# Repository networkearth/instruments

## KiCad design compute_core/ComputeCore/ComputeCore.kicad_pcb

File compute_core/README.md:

# Compute Core

## Requirements

Connections: 
- UART for communication with non-programming devices (2)
- SWD for communication with programming devices (2)
- RST for resetting (1)
- Clock Power (can always be present) (1)
- Power (1)
- GND
(8 pins total)

- Multiplexed I2C (16-2)
  - Programmable address
(14 pins total) 

- Connections for Radio Link (?)
We'll leave this one out for now as this will be a whole adventure unto itself. 

Peripherals
- Real time clock
- External Flash Memory
- Multiplexer for I2C
- LEDs for status

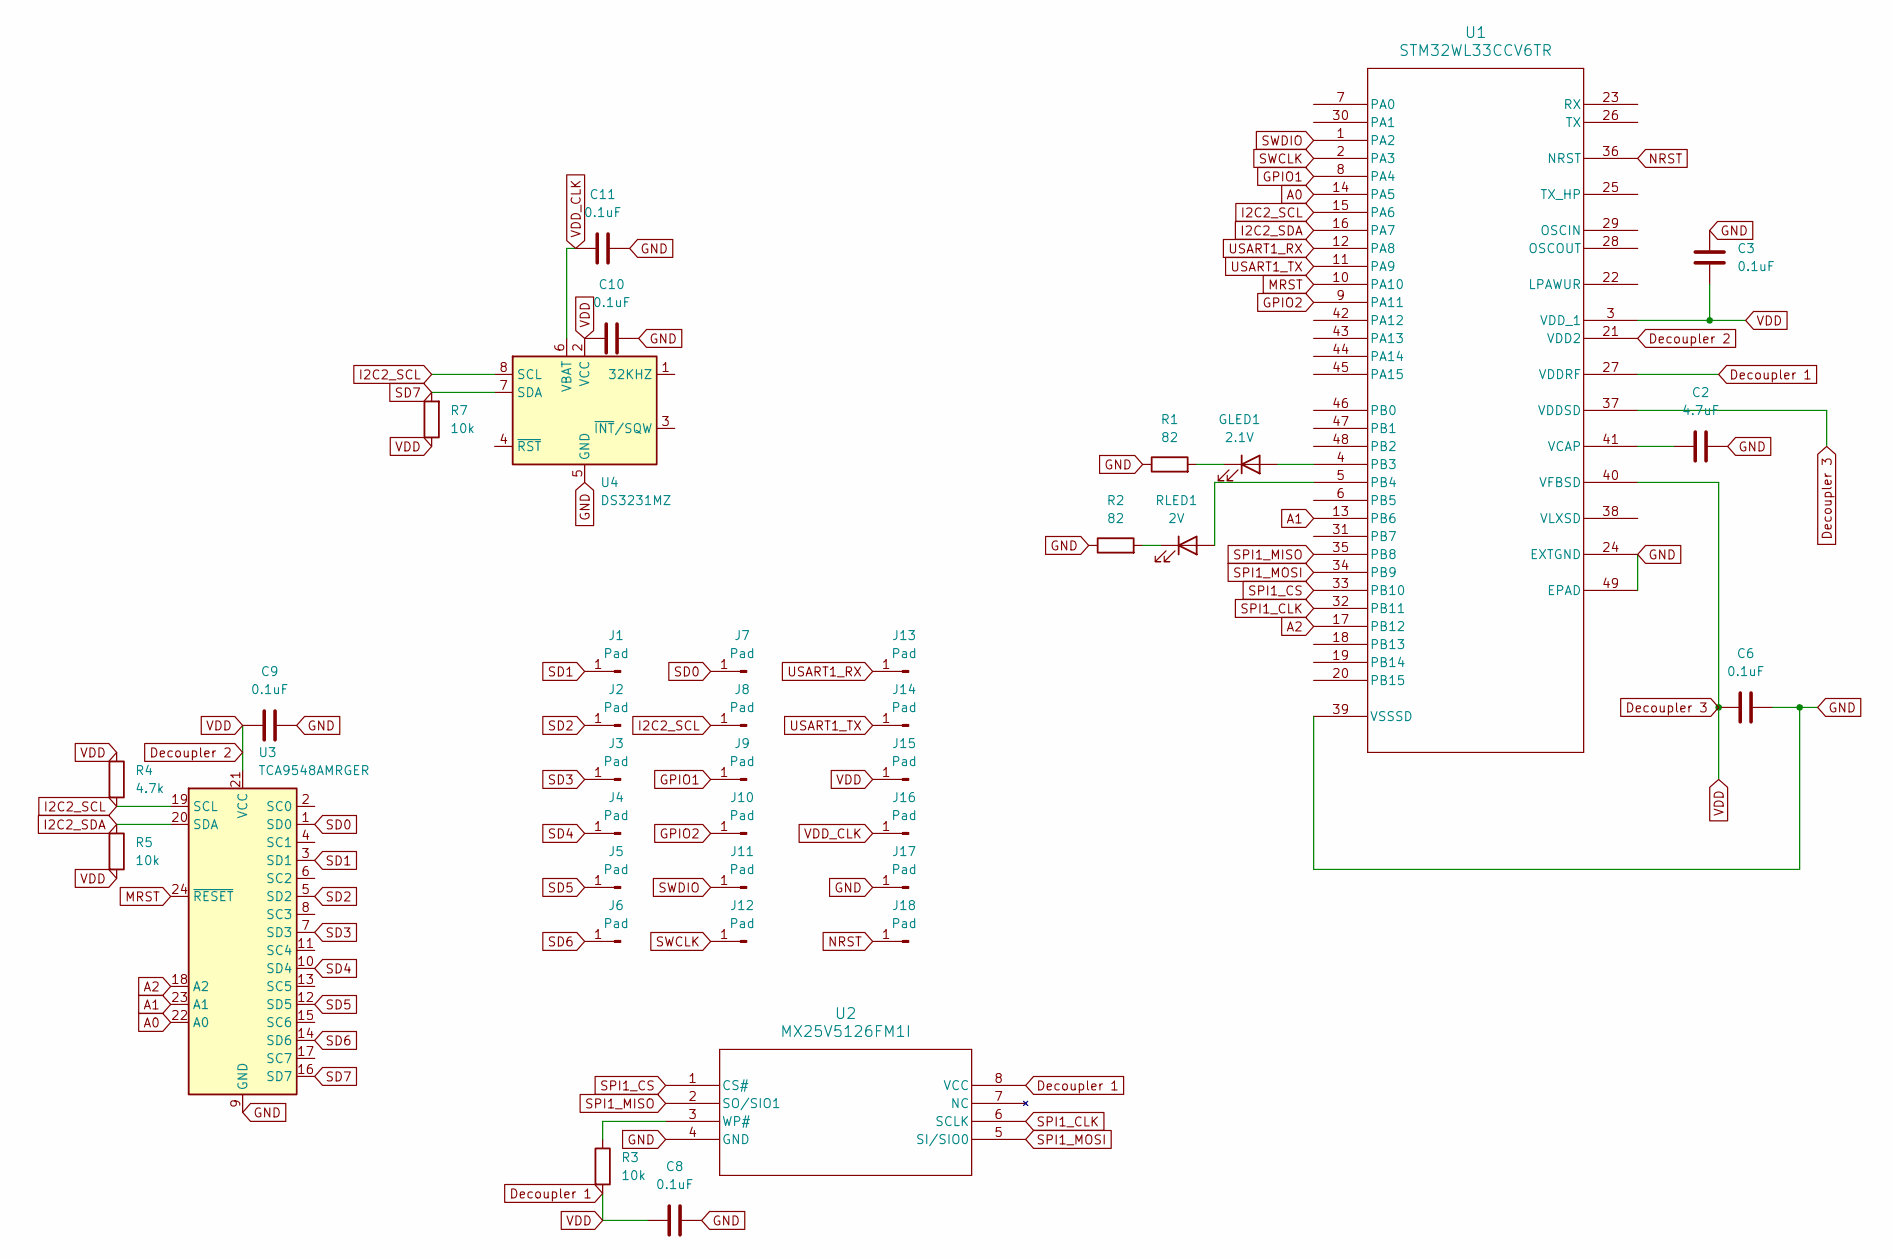
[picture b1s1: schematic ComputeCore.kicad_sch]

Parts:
C2: 4.7uF; C_0201_0603Metric
C3, C6, C8, C9, C10, C11: 0.1uF; C_0201_0603Metric
GLED1: 2.1V; LED_0201_0603Metric
J1, J2, J3, J4, J5, J6, J7, J8, J9, J10, J11, J12, J13, J14, J15, J16, J17, J18: Pad; SolderWire-0.1sqmm_1x01_D0.4mm_OD1mm
R1, R2: 82; R_0201_0603Metric
R3, R5, R7: 10k; R_0201_0603Metric
R4: 4.7k; R_0201_0603Metric
RLED1: 2V; LED_0201_0603Metric
U1: STM32WL33CCV6TR; VFQFPN-48_6x6x0p9mm_STM
U2: MX25V5126FM1I; 8-SOP_MX25V_M1_MAC
U3: TCA9548AMRGER; Texas_RGE0024C_VQFN-24-1EP_4x4mm_P0.5mm_EP2.1x2.1mm
U4: DS3231MZ; SOIC-8_3.9x4.9mm_P1.27mm

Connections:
A0: U1.14 (PA5), U3.22 (A0)
A1: U1.13 (PB6), U3.23 (A1)
A2: U1.17 (PB12), U3.18 (A2)
Decoupler 1: C3.2, C6.1, C8.1, C9.1, C10.1, J15.1, R3.2, R4.1, R5.2, R7.1, U1.3 (VDD_1), U1.21 (VDD2), U1.27 (VDDRF), U1.37 (VDDSD), U1.40 (VFBSD), U2.8 (VCC), U3.21 (VCC), U4.2 (VCC)
GND: C2.2, C3.1, C6.2, C8.2, C9.2, C10.2, C11.2, J17.1, R1.1, R2.1, U1.24 (EXTGND), U1.39 (VSSSD), U1.49 (EPAD), U2.4 (GND), U3.9 (GND), U4.5 (GND)
GPIO1: J9.1, U1.8 (PA4)
GPIO2: J10.1, U1.9 (PA11)
I2C2_SCL: J8.1, R4.2, U1.15 (PA6), U3.19 (SCL), U4.8 (SCL)
I2C2_SDA: R5.1, U1.16 (PA7), U3.20 (SDA)
MRST: U1.10 (PA10), U3.24 (~RESET)
NRST: J18.1, U1.36 (NRST)
unnamed: GLED1.2 (A), U1.4 (PB3)
unnamed: GLED1.1 (K), R1.2
unnamed: RLED1.2 (A), U1.5 (PB4)
unnamed: R2.2, RLED1.1 (K)
unnamed: C2.1, U1.41 (VCAP)
unnamed: R3.1, U2.3 (WP#)
SD0: J7.1, U3.1 (SD0)
SD1: J1.1, U3.3 (SD1)
SD2: J2.1, U3.5 (SD2)
SD3: J3.1, U3.7 (SD3)
SD4: J4.1, U3.10 (SD4)
SD5: J5.1, U3.12 (SD5)
SD6: J6.1, U3.14 (SD6)
SD7: R7.2, U3.16 (SD7), U4.7 (SDA)
SPI1_CLK: U1.32 (PB11), U2.6 (SCLK)
SPI1_CS: U1.33 (PB10), U2.1 (CS#)
SPI1_MISO: U1.35 (PB8), U2.2 (SO/SIO1)
SPI1_MOSI: U1.34 (PB9), U2.5 (SI/SIO0)
SWCLK: J12.1, U1.2 (PA3)
SWDIO: J11.1, U1.1 (PA2)
USART1_RX: J13.1, U1.12 (PA8)
USART1_TX: J14.1, U1.11 (PA9)
VDD_CLK: C11.1, J16.1, U4.6 (VBAT)

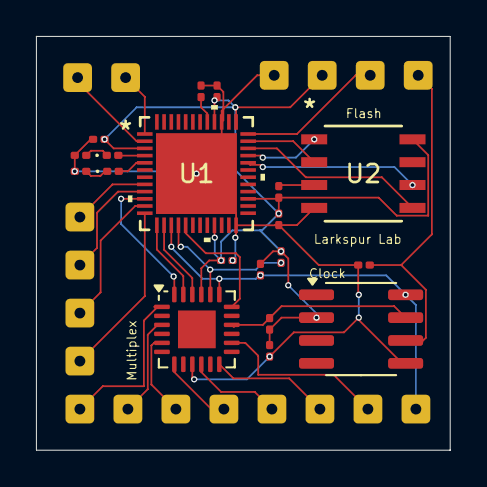
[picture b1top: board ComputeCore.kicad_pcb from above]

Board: 2 copper layers, 23.0 x 23.0 mm, 37 parts (0 on the bottom side), 34 nets.

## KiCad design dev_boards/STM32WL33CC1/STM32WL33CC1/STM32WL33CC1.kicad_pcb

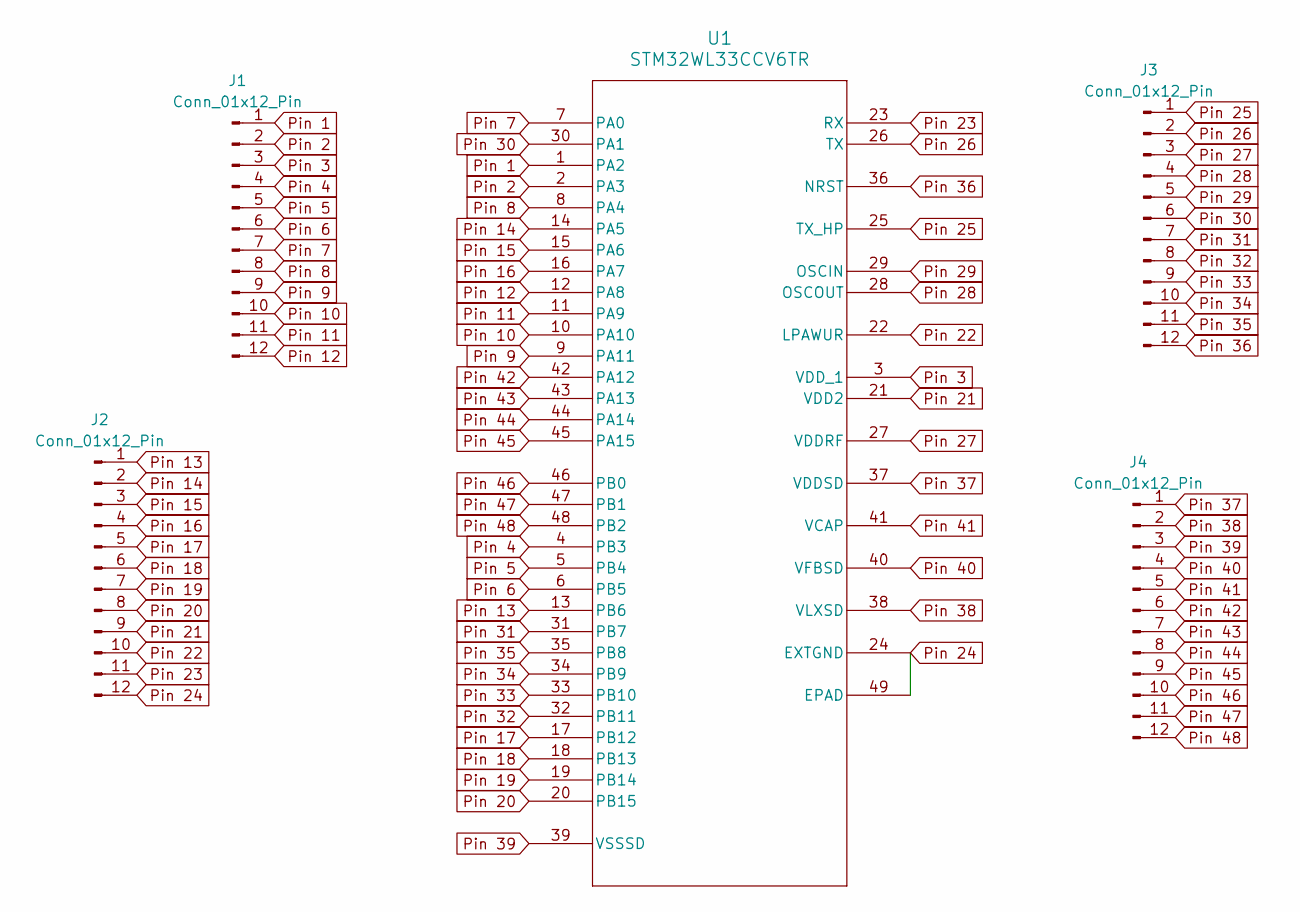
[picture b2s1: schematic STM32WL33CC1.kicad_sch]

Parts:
J1, J2, J3, J4: Conn_01x12_Pin; PinHeader_1x12_P2.54mm_Vertical
U1: STM32WL33CCV6TR; VFQFPN-48_6x6x0p9mm_STM

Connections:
Pin 1: J1.1, U1.1 (PA2)
Pin 2: J1.2, U1.2 (PA3)
Pin 3: J1.3, U1.3 (VDD_1)
Pin 4: J1.4, U1.4 (PB3)
Pin 5: J1.5, U1.5 (PB4)
Pin 6: J1.6, U1.6 (PB5)
Pin 7: J1.7, U1.7 (PA0)
Pin 8: J1.8, U1.8 (PA4)
Pin 9: J1.9, U1.9 (PA11)
Pin 10: J1.10, U1.10 (PA10)
Pin 11: J1.11, U1.11 (PA9)
Pin 12: J1.12, U1.12 (PA8)
Pin 13: J2.1, U1.13 (PB6)
Pin 14: J2.2, U1.14 (PA5)
Pin 15: J2.3, U1.15 (PA6)
Pin 16: J2.4, U1.16 (PA7)
Pin 17: J2.5, U1.17 (PB12)
Pin 18: J2.6, U1.18 (PB13)
Pin 19: J2.7, U1.19 (PB14)
Pin 20: J2.8, U1.20 (PB15)
Pin 21: J2.9, U1.21 (VDD2)
Pin 22: J2.10, U1.22 (LPAWUR)
Pin 23: J2.11, U1.23 (RX)
Pin 24: J2.12, U1.24 (EXTGND), U1.49 (EPAD)
Pin 25: J3.1, U1.25 (TX_HP)
Pin 26: J3.2, U1.26 (TX)
Pin 27: J3.3, U1.27 (VDDRF)
Pin 28: J3.4, U1.28 (OSCOUT)
Pin 29: J3.5, U1.29 (OSCIN)
Pin 30: J3.6, U1.30 (PA1)
Pin 31: J3.7, U1.31 (PB7)
Pin 32: J3.8, U1.32 (PB11)
Pin 33: J3.9, U1.33 (PB10)
Pin 34: J3.10, U1.34 (PB9)
Pin 35: J3.11, U1.35 (PB8)
Pin 36: J3.12, U1.36 (NRST)
Pin 37: J4.1, U1.37 (VDDSD)
Pin 38: J4.2, U1.38 (VLXSD)
Pin 39: J4.3, U1.39 (VSSSD)
Pin 40: J4.4, U1.40 (VFBSD)
Pin 41: J4.5, U1.41 (VCAP)
Pin 42: J4.6, U1.42 (PA12)
Pin 43: J4.7, U1.43 (PA13)
Pin 44: J4.8, U1.44 (PA14)
Pin 45: J4.9, U1.45 (PA15)
Pin 46: J4.10, U1.46 (PB0)
Pin 47: J4.11, U1.47 (PB1)
Pin 48: J4.12, U1.48 (PB2)

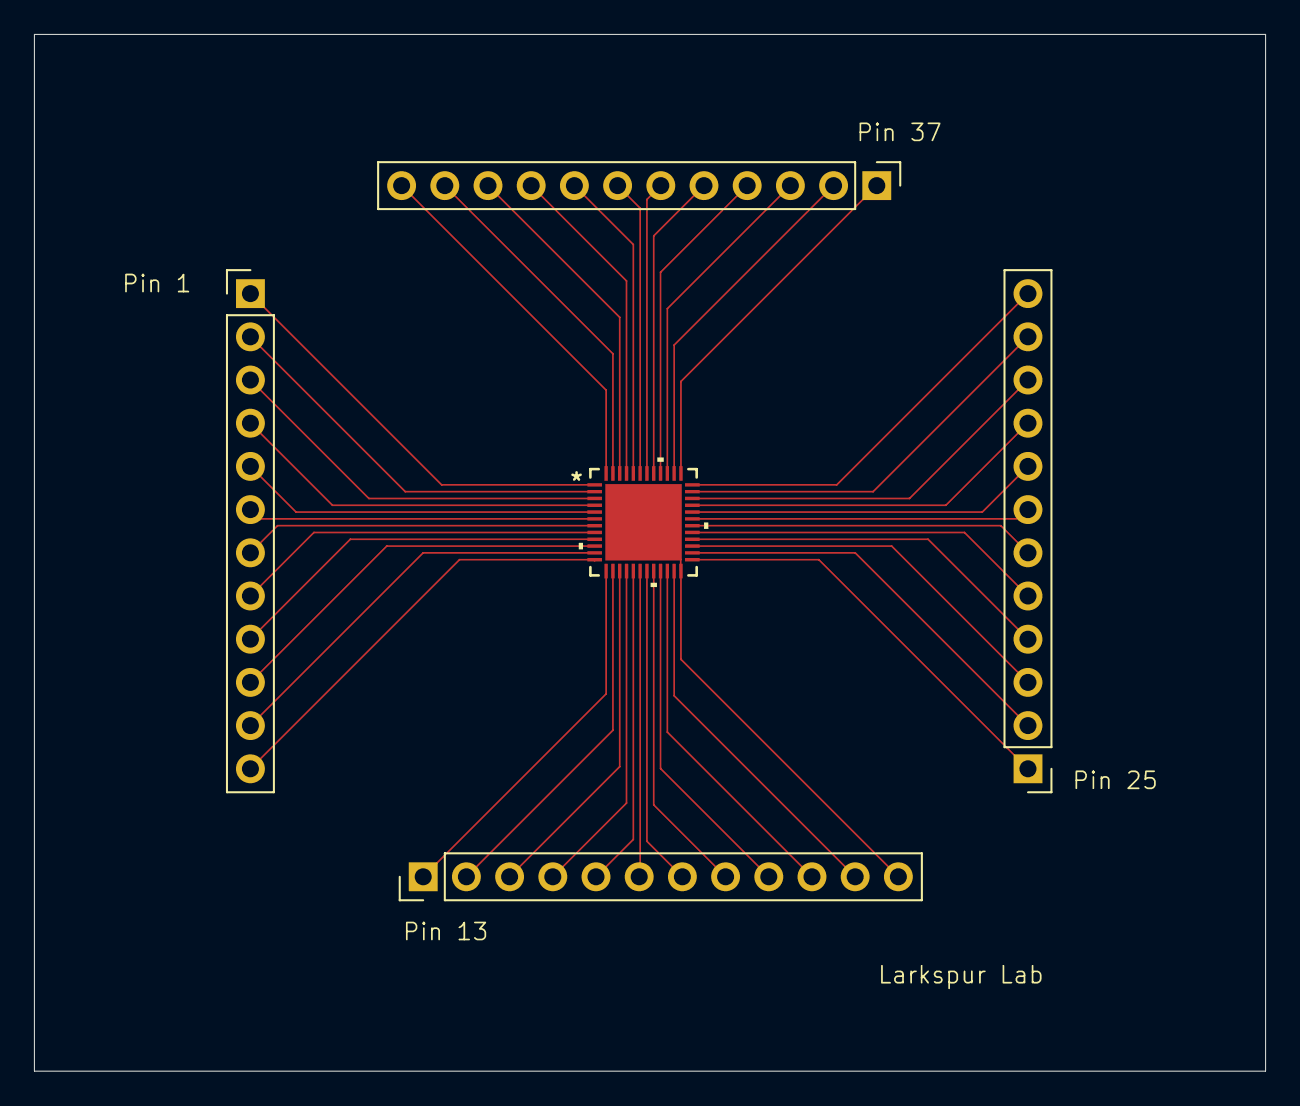
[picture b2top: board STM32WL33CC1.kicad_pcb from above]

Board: 2 copper layers, 72.4 x 61.0 mm, 5 parts (0 on the bottom side), 48 nets.

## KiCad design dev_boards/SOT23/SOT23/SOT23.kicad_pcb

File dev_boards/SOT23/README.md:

# Bits and Bobs

Loads of things come in an **SOT23** package.

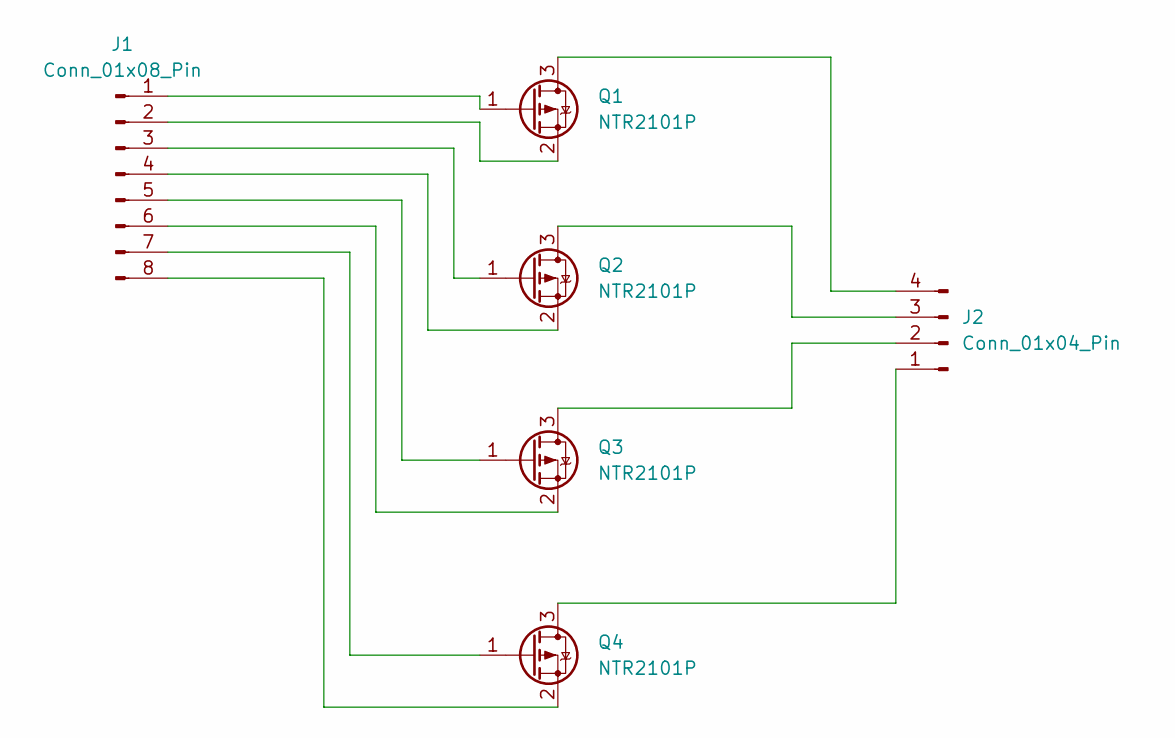
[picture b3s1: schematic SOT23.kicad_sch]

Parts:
J1: Conn_01x08_Pin; PinHeader_1x08_P2.54mm_Vertical
J2: Conn_01x04_Pin; PinHeader_1x04_P2.54mm_Vertical
Q1, Q2, Q3, Q4: NTR2101P; SOT-23

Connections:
unnamed: J1.1, Q1.1 (G)
unnamed: J1.2, Q1.2 (S)
unnamed: J1.3, Q2.1 (G)
unnamed: J1.4, Q2.2 (S)
unnamed: J1.5, Q3.1 (G)
unnamed: J1.6, Q3.2 (S)
unnamed: J1.7, Q4.1 (G)
unnamed: J1.8, Q4.2 (S)
unnamed: J2.1, Q4.3 (D)
unnamed: J2.2, Q3.3 (D)
unnamed: J2.3, Q2.3 (D)
unnamed: J2.4, Q1.3 (D)

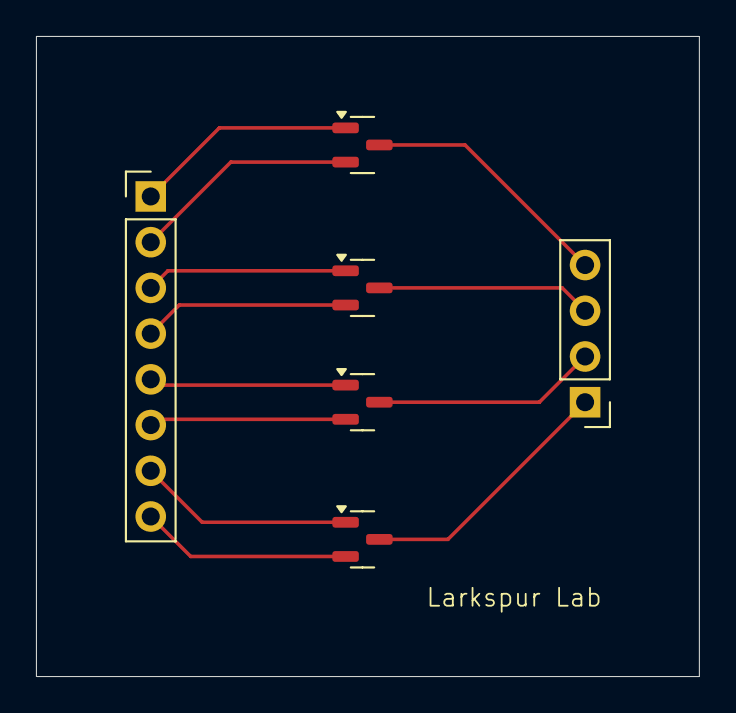
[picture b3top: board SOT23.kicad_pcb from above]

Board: 2 copper layers, 36.8 x 35.6 mm, 6 parts (0 on the bottom side), 12 nets.

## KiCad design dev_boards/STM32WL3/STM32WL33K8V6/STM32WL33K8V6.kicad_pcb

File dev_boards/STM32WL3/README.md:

# Microcontroller Unit (MCU)

Digital radio communication is fantastically interesting and like many fascinating things it is pretty darn complicated. So isn't it wonderful that ST has chips and software that come with everything you need to manage the communication! All at low power too.

- [STM32WL3 Line](https://www.st.com/content/st_com/en/campaigns/stm32wl3-comprehensive-ecosystem-long-range-iot-connectivity-z13.html?ecmp=tt45044_gl_ps_jun2025&aw_kw=stm32%20wireless%20mcus&aw_m=e&aw_c=22032657977&aw_tg=aud-2173644794635:kwd-1457438729886&aw_gclid=CjwKCAjwprjDBhBTEiwA1m1d0oSMdFI7UCsje4d8FfuBJjFW-EInW3rT8UjZ1rWWHqVwe16UJWC6EBoCuuIQAvD_BwE&gad_source=1&gad_campaignid=22032657977&gbraid=0AAAAADmP1XT8bcmLf6zb8UZTWm7Z2yrFH&gclid=CjwKCAjwprjDBhBTEiwA1m1d0oSMdFI7UCsje4d8FfuBJjFW-EInW3rT8UjZ1rWWHqVwe16UJWC6EBoCuuIQAvD_BwE)
- [Kineis Constellation](https://blog.st.com/kineis/) (works with STM32's)
- [Kineis Stack](https://www.st.com/content/st_com/en/partner/partner-program/partnerpage/Kineis.html)
- [Reference Design](https://kineis.com/en/kineis-stack-for-a-quick-integration-2/)
- [and it's part of the CLS (Argos) ecosystem!](https://telemetry.groupcls.com/argos-solutions/argos-products/modems/)

All in all pretty sweet. What we need is one that's integrated with I2C and SPI for communication with sensors and memory as well. The [STM32WL33K8V6](https://www.digikey.com/en/products/detail/stmicroelectronics/STM32WL33K8V6/22519707) fits the bill pretty well. This uses a **32-VFQFN Exposed Pad** footprint so we can reuse this development board for anything with this footprint.

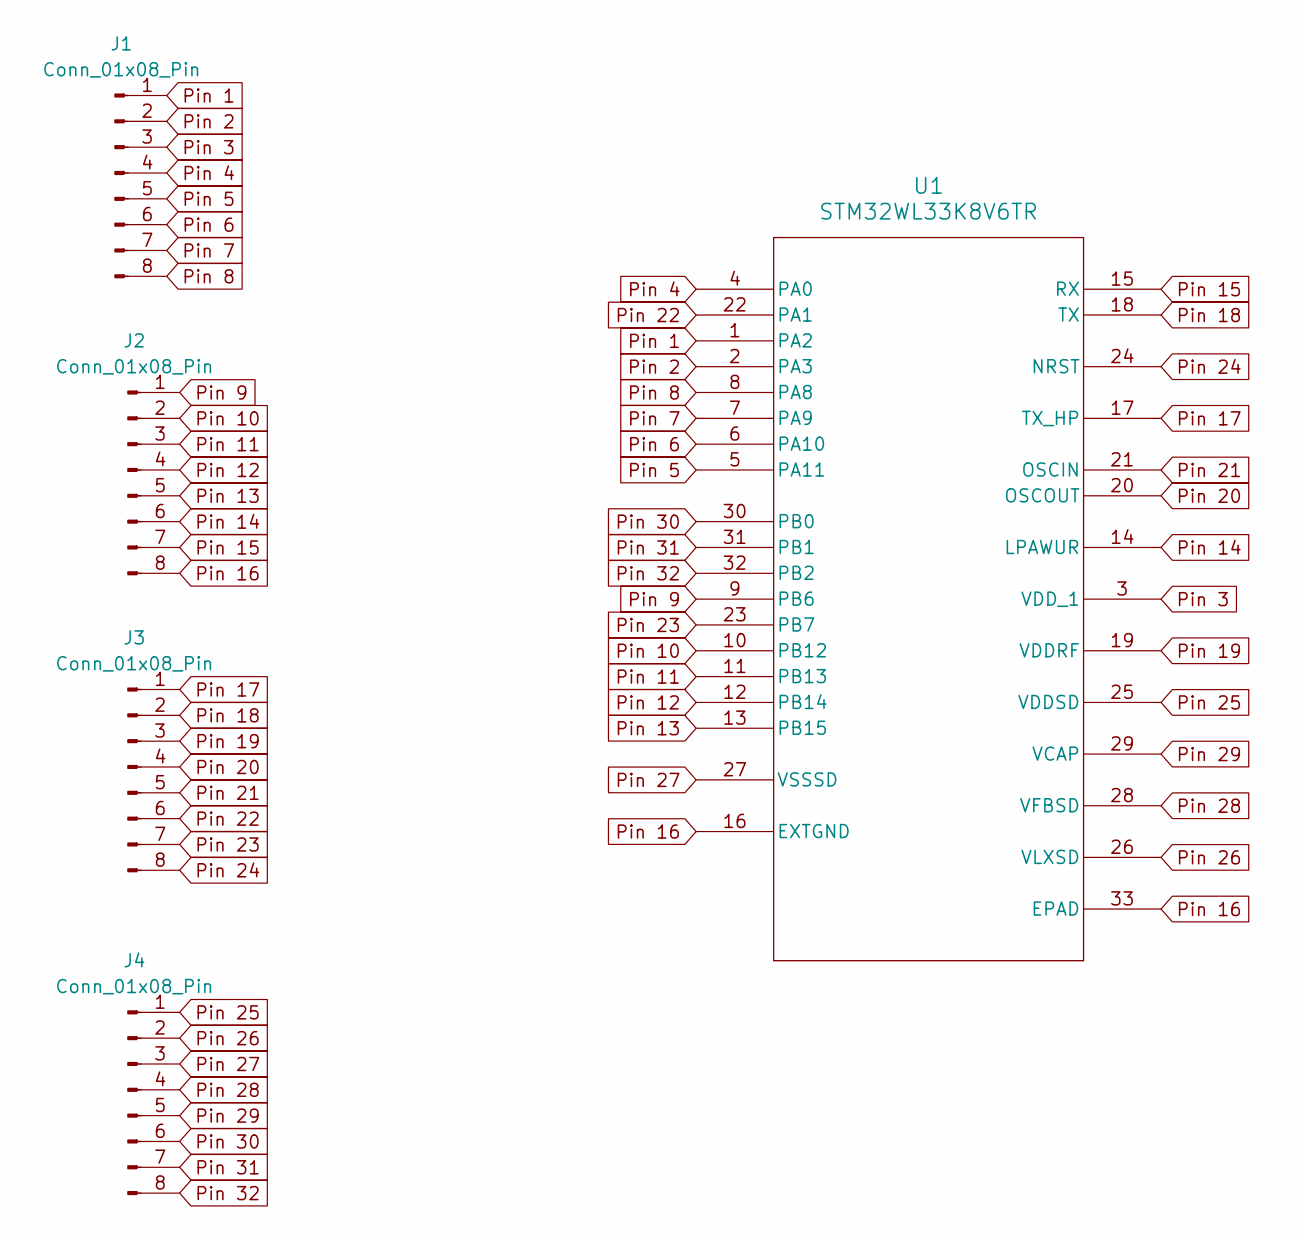
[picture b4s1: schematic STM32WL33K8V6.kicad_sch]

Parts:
J1, J2, J3, J4: Conn_01x08_Pin; PinHeader_1x08_P2.54mm_Vertical
U1: STM32WL33K8V6TR; VFQFPN-32_5x5x1mm_STM

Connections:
Pin 1: J1.1, U1.1 (PA2)
Pin 2: J1.2, U1.2 (PA3)
Pin 3: J1.3, U1.3 (VDD_1)
Pin 4: J1.4, U1.4 (PA0)
Pin 5: J1.5, U1.5 (PA11)
Pin 6: J1.6, U1.6 (PA10)
Pin 7: J1.7, U1.7 (PA9)
Pin 8: J1.8, U1.8 (PA8)
Pin 9: J2.1, U1.9 (PB6)
Pin 10: J2.2, U1.10 (PB12)
Pin 11: J2.3, U1.11 (PB13)
Pin 12: J2.4, U1.12 (PB14)
Pin 13: J2.5, U1.13 (PB15)
Pin 14: J2.6, U1.14 (LPAWUR)
Pin 15: J2.7, U1.15 (RX)
Pin 16: J2.8, U1.16 (EXTGND), U1.33 (EPAD)
Pin 17: J3.1, U1.17 (TX_HP)
Pin 18: J3.2, U1.18 (TX)
Pin 19: J3.3, U1.19 (VDDRF)
Pin 20: J3.4, U1.20 (OSCOUT)
Pin 21: J3.5, U1.21 (OSCIN)
Pin 22: J3.6, U1.22 (PA1)
Pin 23: J3.7, U1.23 (PB7)
Pin 24: J3.8, U1.24 (NRST)
Pin 25: J4.1, U1.25 (VDDSD)
Pin 26: J4.2, U1.26 (VLXSD)
Pin 27: J4.3, U1.27 (VSSSD)
Pin 28: J4.4, U1.28 (VFBSD)
Pin 29: J4.5, U1.29 (VCAP)
Pin 30: J4.6, U1.30 (PB0)
Pin 31: J4.7, U1.31 (PB1)
Pin 32: J4.8, U1.32 (PB2)

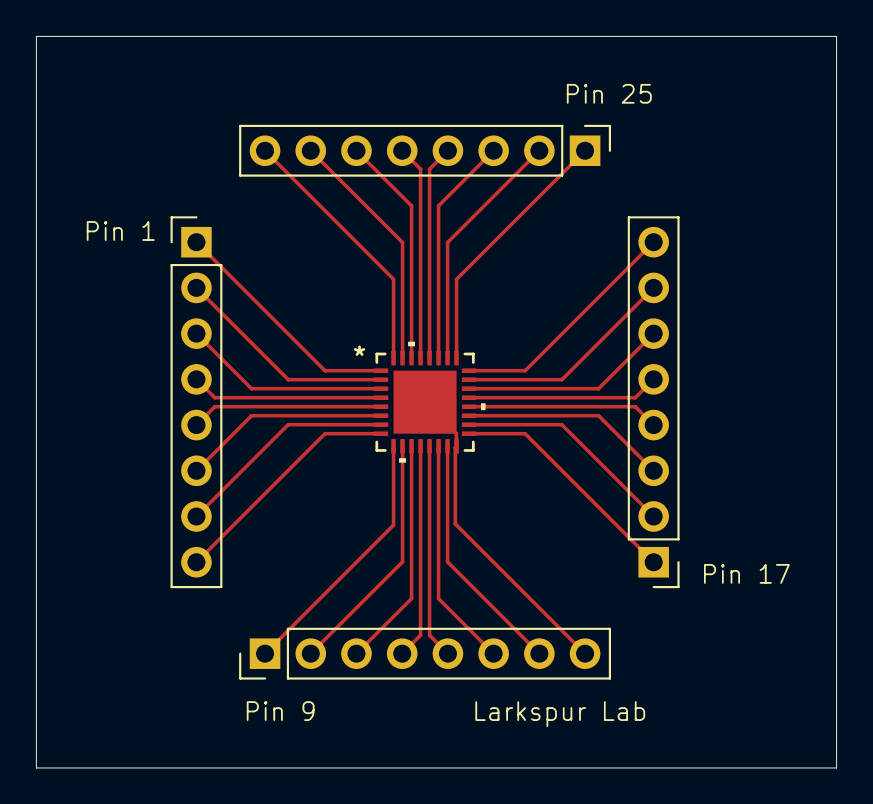
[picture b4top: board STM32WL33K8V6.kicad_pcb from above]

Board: 2 copper layers, 44.5 x 40.6 mm, 5 parts (0 on the bottom side), 32 nets.

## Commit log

2025-07-09 stm32
2025-07-19 temperature sensor
2025-07-19 flash memory
2025-07-19 bits and bobs
2025-07-19 let there be light
2025-07-19 some cad files I forgot
2025-07-19 some links
2025-08-22 48 pins
2025-08-22 temp sensor
2025-08-24 storage
2025-09-19 compute core wip
